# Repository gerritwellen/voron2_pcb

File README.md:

# voron2_pcb
Breakout PCBs for Voron2.4

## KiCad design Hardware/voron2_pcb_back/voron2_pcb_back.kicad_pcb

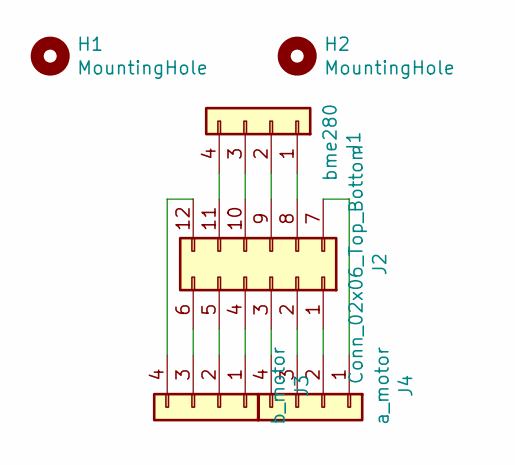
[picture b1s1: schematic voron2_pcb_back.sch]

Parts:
H1, H2: MountingHole; MountingHole_3.2mm_M3
J1: bme280; JST_XH_B4B-XH-A_1x04_P2.50mm_Vertical
J2: Conn_02x06_Top_Bottom; Molex_Micro-Fit_3.0_43045-1212_2x06_P3.00mm_Vertical
J3: b_motor; JST_XH_B4B-XH-A_1x04_P2.50mm_Vertical
J4: a_motor; JST_XH_B4B-XH-A_1x04_P2.50mm_Vertical

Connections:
unnamed: J1.1, J2.8
unnamed: J1.2, J2.9
unnamed: J1.3, J2.10
unnamed: J1.4, J2.11
unnamed: J2.1, J4.2
unnamed: J2.2, J4.3
unnamed: J2.3, J4.4
unnamed: J2.4, J3.1
unnamed: J2.5, J3.2
unnamed: J2.6, J3.3
unnamed: J2.7, J4.1
unnamed: J2.12, J3.4

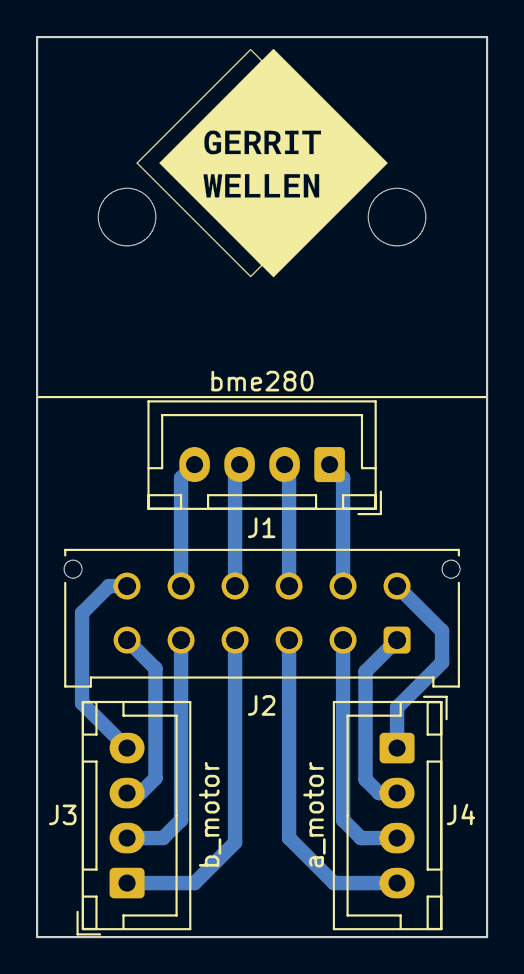
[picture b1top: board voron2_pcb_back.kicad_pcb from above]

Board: 2 copper layers, 25.0 x 50.0 mm, 6 parts (0 on the bottom side), 12 nets.

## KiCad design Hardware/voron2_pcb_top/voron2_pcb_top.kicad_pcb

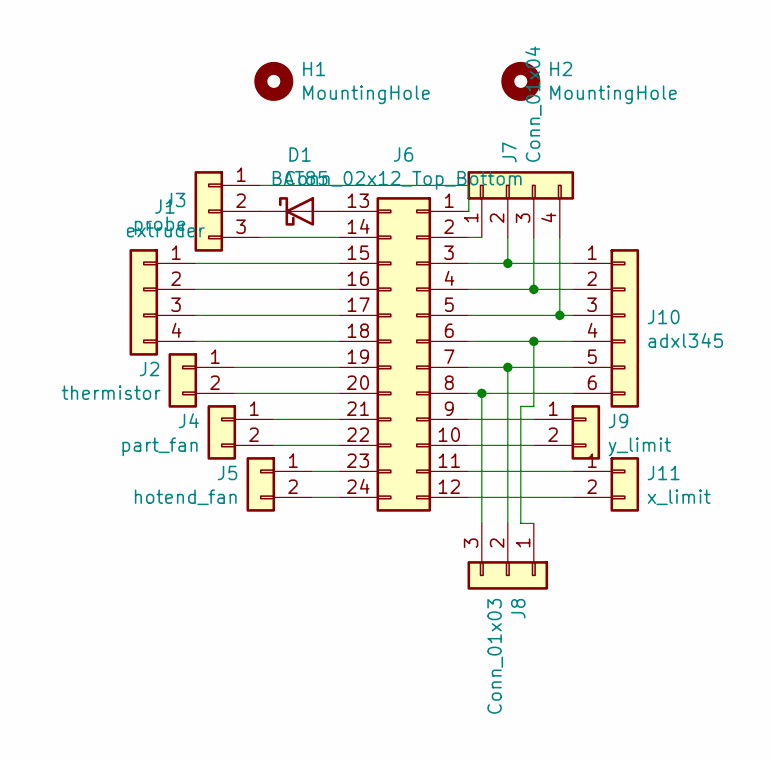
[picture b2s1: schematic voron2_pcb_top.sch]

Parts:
D1: BAT85; D_DO-35_SOD27_P7.62mm_Horizontal
H1, H2: MountingHole; MountingHole_3.2mm_M3
J1: extruder; JST_XH_B4B-XH-A_1x04_P2.50mm_Vertical
J2: thermistor; JST_XH_B2B-XH-A_1x02_P2.50mm_Vertical
J3: probe; JST_XH_B3B-XH-A_1x03_P2.50mm_Vertical
J4: part_fan; JST_XH_B2B-XH-A_1x02_P2.50mm_Vertical
J5: hotend_fan; JST_XH_B2B-XH-A_1x02_P2.50mm_Vertical
J6: Conn_02x12_Top_Bottom; Molex_Micro-Fit_3.0_43045-2412_2x12_P3.00mm_Vertical
J7: Conn_01x04; PinHeader_1x04_P2.54mm_Vertical
J8: Conn_01x03; PinHeader_1x03_P2.54mm_Vertical
J9: y_limit; JST_XH_B2B-XH-A_1x02_P2.50mm_Vertical
J10: adxl345; JST_XH_B6B-XH-A_1x06_P2.50mm_Vertical
J11: x_limit; JST_XH_B2B-XH-A_1x02_P2.50mm_Vertical

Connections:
unnamed: D1.1 (K), J3.2
unnamed: D1.2 (A), J6.13
unnamed: J1.1, J6.15
unnamed: J1.2, J6.16
unnamed: J1.3, J6.17
unnamed: J1.4, J6.18
unnamed: J2.1, J6.19
unnamed: J2.2, J6.20
unnamed: J3.1, J6.1
unnamed: J3.3, J6.14
unnamed: J4.1, J6.21
unnamed: J4.2, J6.22
unnamed: J5.1, J6.23
unnamed: J5.2, J6.24
unnamed: J6.2, J7.1
unnamed: J6.9, J9.1
unnamed: J6.10, J9.2
unnamed: J6.3, J7.2, J10.1
unnamed: J6.4, J7.3, J10.2
unnamed: J6.5, J7.4, J10.3
unnamed: J6.6, J8.1, J10.4
unnamed: J6.7, J8.2, J10.5
unnamed: J6.8, J8.3, J10.6
unnamed: J6.11, J11.1
unnamed: J6.12, J11.2

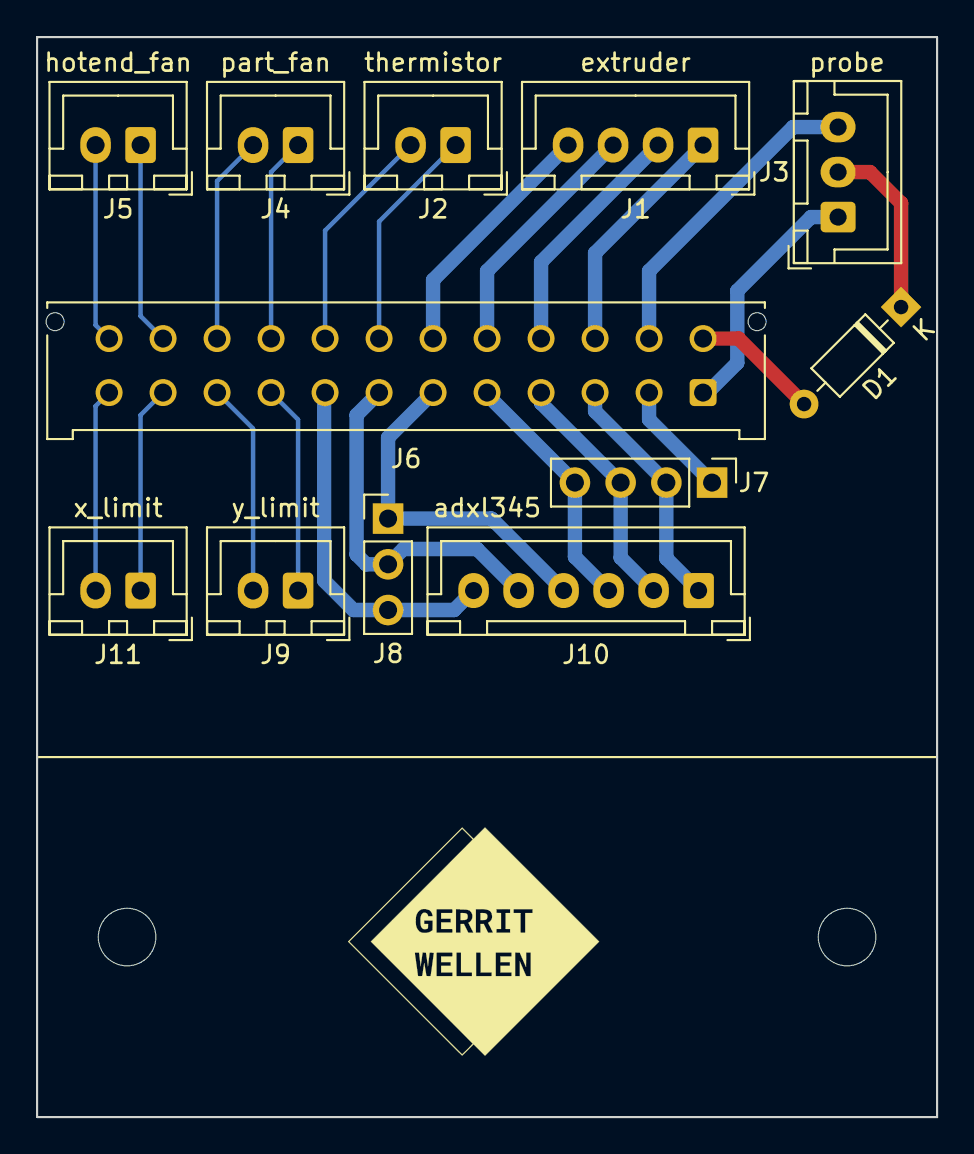
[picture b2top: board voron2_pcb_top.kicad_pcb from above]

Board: 2 copper layers, 50.0 x 60.0 mm, 14 parts (0 on the bottom side), 25 nets.

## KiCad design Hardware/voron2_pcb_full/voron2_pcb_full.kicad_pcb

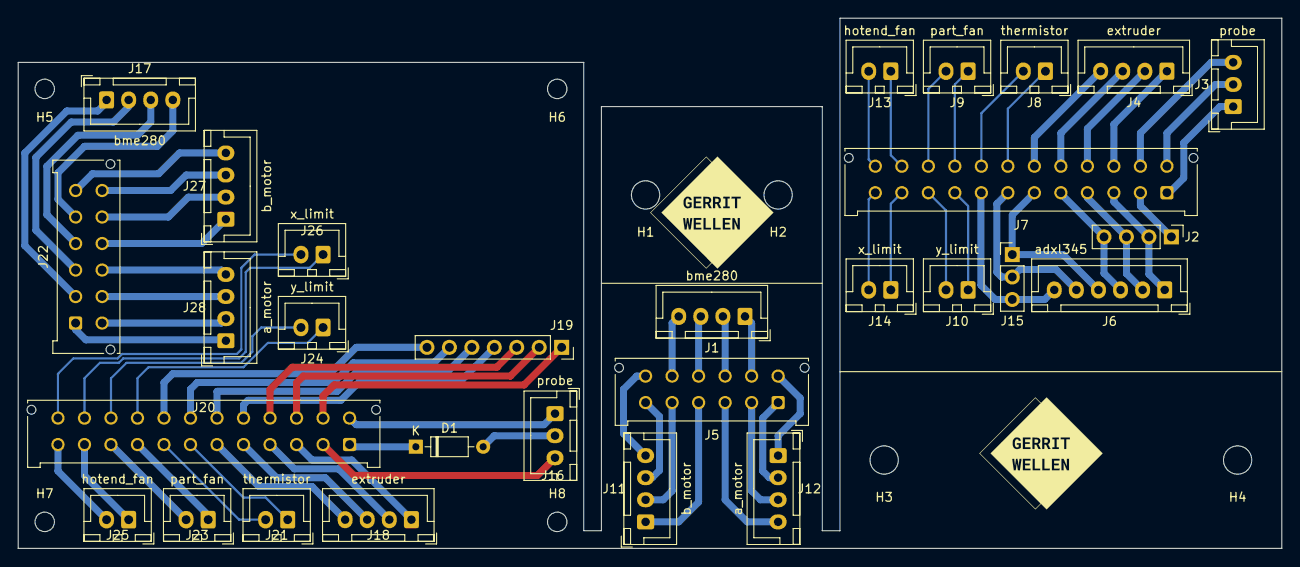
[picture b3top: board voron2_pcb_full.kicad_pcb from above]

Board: 2 copper layers, 143.0 x 60.0 mm, 37 parts (0 on the bottom side), 73 nets.

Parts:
D1: BAT85; D_DO-35_SOD27_P7.62mm_Horizontal
H1, H2, H3, H4: MountingHole; MountingHole_3.2mm_M3
H5, H6, H7, H8: MountingHole; MountingHole_2.2mm_M2
J1, J17: bme280; JST_XH_B4B-XH-A_1x04_P2.50mm_Vertical
J2: Conn_01x04; PinHeader_1x04_P2.54mm_Vertical
J3, J16: probe; JST_XH_B3B-XH-A_1x03_P2.50mm_Vertical
J4, J18: extruder; JST_XH_B4B-XH-A_1x04_P2.50mm_Vertical
J5, J22: Conn_02x06_Top_Bottom; Molex_Micro-Fit_3.0_43045-1212_2x06_P3.00mm_Vertical
J6: adxl345; JST_XH_B6B-XH-A_1x06_P2.50mm_Vertical
J7, J20: Conn_02x12_Top_Bottom; Molex_Micro-Fit_3.0_43045-2412_2x12_P3.00mm_Vertical
J8, J21: thermistor; JST_XH_B2B-XH-A_1x02_P2.50mm_Vertical
J9, J23: part_fan; JST_XH_B2B-XH-A_1x02_P2.50mm_Vertical
J10, J24: y_limit; JST_XH_B2B-XH-A_1x02_P2.50mm_Vertical
J11, J27: b_motor; JST_XH_B4B-XH-A_1x04_P2.50mm_Vertical
J12, J28: a_motor; JST_XH_B4B-XH-A_1x04_P2.50mm_Vertical
J13, J25: hotend_fan; JST_XH_B2B-XH-A_1x02_P2.50mm_Vertical
J14, J26: x_limit; JST_XH_B2B-XH-A_1x02_P2.50mm_Vertical
J15: Conn_01x03; PinHeader_1x03_P2.54mm_Vertical
J19: Conn_01x07; PinSocket_1x07_P2.54mm_Vertical

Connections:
unnamed: D1.1, J20.1
unnamed: D1.2, J16.2
unnamed: J1.1, J5.8
unnamed: J1.2, J5.9
unnamed: J1.3, J5.10
unnamed: J1.4, J5.11
unnamed: J2.1, J7.2
unnamed: J2.2, J6.1, J7.3
unnamed: J2.3, J6.2, J7.4
unnamed: J2.4, J6.3, J7.5
unnamed: J3.1, J7.1
unnamed: J3.2, J7.13
unnamed: J3.3, J7.14
unnamed: J4.1, J7.15
unnamed: J4.2, J7.16
unnamed: J4.3, J7.17
unnamed: J4.4, J7.18
unnamed: J7.19, J8.1
unnamed: J7.20, J8.2
unnamed: J7.21, J9.1
unnamed: J7.22, J9.2
unnamed: J7.9, J10.1
unnamed: J7.10, J10.2
unnamed: J5.4, J11.1
unnamed: J5.5, J11.2
unnamed: J5.6, J11.3
unnamed: J5.12, J11.4
unnamed: J5.7, J12.1
unnamed: J5.1, J12.2
unnamed: J5.2, J12.3
unnamed: J5.3, J12.4
unnamed: J7.23, J13.1
unnamed: J7.24, J13.2
unnamed: J7.11, J14.1
unnamed: J7.12, J14.2
unnamed: J6.4, J7.6, J15.1
unnamed: J6.5, J7.7, J15.2
unnamed: J6.6, J7.8, J15.3
unnamed: J16.1, J20.13
unnamed: J16.3, J20.2
unnamed: J17.1, J22.2
unnamed: J17.2, J22.3
unnamed: J17.3, J22.4
unnamed: J17.4, J22.5
unnamed: J18.1, J20.3
unnamed: J18.2, J20.4
unnamed: J18.3, J20.5
unnamed: J18.4, J20.6
unnamed: J19.1, J20.14
unnamed: J19.2, J20.15
unnamed: J19.3, J20.16
unnamed: J19.4, J20.17
unnamed: J19.5, J20.18
unnamed: J19.6, J20.19
unnamed: J19.7, J20.20
unnamed: J20.7, J21.1
unnamed: J20.8, J21.2
unnamed: J20.9, J23.1
unnamed: J20.10, J23.2
unnamed: J20.11, J25.1
unnamed: J20.12, J25.2
unnamed: J20.21, J24.1
unnamed: J20.22, J24.2
unnamed: J20.23, J26.1
unnamed: J20.24, J26.2
unnamed: J22.1, J28.1
unnamed: J22.6, J27.4
unnamed: J22.7, J28.2
unnamed: J22.8, J28.3
unnamed: J22.9, J28.4
unnamed: J22.10, J27.1
unnamed: J22.11, J27.2
unnamed: J22.12, J27.3

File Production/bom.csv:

"Id";"Designator";"Package";"Quantity";"Designation";"Supplier and ref";
1;"J28,J12";"JST_XH_B4B-XH-A_1x04_P2.50mm_Vertical";2;"a_motor";;;
2;"J27,J11";"JST_XH_B4B-XH-A_1x04_P2.50mm_Vertical";2;"b_motor";;;
3;"J26,J14";"JST_XH_B2B-XH-A_1x02_P2.50mm_Vertical";2;"x_limit";;;
4;"J25,J13";"JST_XH_B2B-XH-A_1x02_P2.50mm_Vertical";2;"hotend_fan";;;
5;"J24,J10";"JST_XH_B2B-XH-A_1x02_P2.50mm_Vertical";2;"y_limit";;;
6;"J23,J9";"JST_XH_B2B-XH-A_1x02_P2.50mm_Vertical";2;"part_fan";;;
7;"J22,J5";"Molex_Micro-Fit_3.0_43045-1212_2x06_P3.00mm_Vertical";2;"Conn_02x06_Top_Bottom";;;
8;"J21,J8";"JST_XH_B2B-XH-A_1x02_P2.50mm_Vertical";2;"thermistor";;;
9;"J20,J7";"Molex_Micro-Fit_3.0_43045-2412_2x12_P3.00mm_Vertical";2;"Conn_02x12_Top_Bottom";;;
10;"J19";"PinSocket_1x07_P2.54mm_Vertical";1;"Conn_01x07";;;
11;"J18,J4";"JST_XH_B4B-XH-A_1x04_P2.50mm_Vertical";2;"extruder";;;
12;"J17,J1";"JST_XH_B4B-XH-A_1x04_P2.50mm_Vertical";2;"bme280";;;
13;"J16,J3";"JST_XH_B3B-XH-A_1x03_P2.50mm_Vertical";2;"probe";;;
14;"J15";"PinHeader_1x03_P2.54mm_Vertical";1;"Conn_01x03";;;
15;"J6";"JST_XH_B6B-XH-A_1x06_P2.50mm_Vertical";1;"adxl345";;;
16;"J2";"PinHeader_1x04_P2.54mm_Vertical";1;"Conn_01x04";;;
17;"H8,H7,H6,H5";"MountingHole_2.2mm_M2";4;"MountingHole";;;
18;"H4,H3,H2,H1";"MountingHole_3.2mm_M3";4;"MountingHole";;;
19;"D1";"D_DO-35_SOD27_P7.62mm_Horizontal";1;"BAT85";;;

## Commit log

2021-02-21 Added License
2021-02-21 Moved necessary files into repository.
2021-03-03 Added Varriant without Base Board
2021-03-03 Added Gerber Files for Top Only Cleaned Up File Structure
2021-03-03 Fixed Gerber Files
2021-03-03 Added Logo And JCLPCB Order Number Location
2021-03-03 Added BAT85 diode to top breakoutboard in top only option.
    Added rendered image of top option.
2021-03-04 Separated top in top and back for easier production.
    Added renders of top and back PCBs.
2021-04-18 img: added Pictures, production: added no_logo-versions
    Added pictures of the PCBs blank and assembled.
    Added version without the Logo.
